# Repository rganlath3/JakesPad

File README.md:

# JakesPad
A custom built fighting gamepad controller for arcade style games. This controller is custom sized for "Jake". It uses a raspberry pi 2040 chipset along with Kailh keyswitches with a custom 3D printed enclosure and PCB.
This is based on jfedor2's flatbox rev5 design. I reverse engineered the PCB from his design here: https://github.com/jfedor2/flatbox.git

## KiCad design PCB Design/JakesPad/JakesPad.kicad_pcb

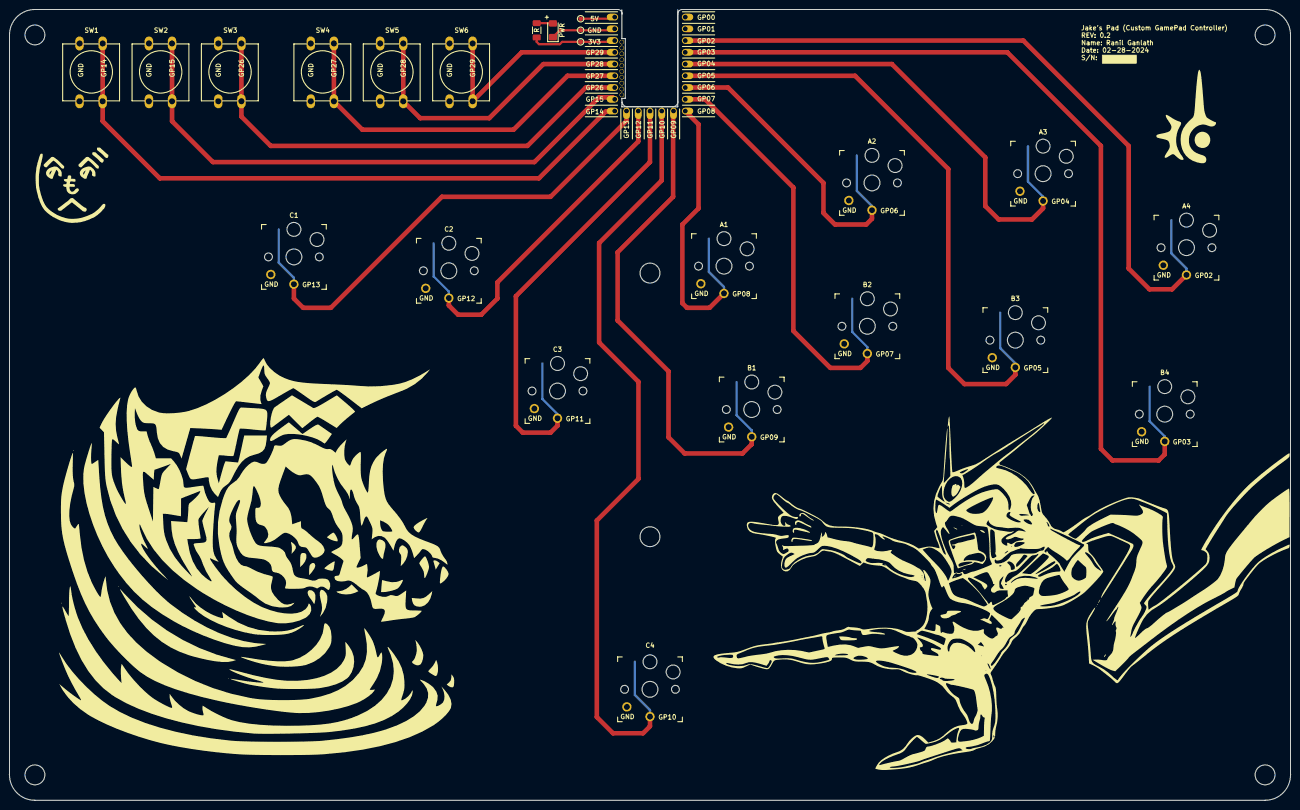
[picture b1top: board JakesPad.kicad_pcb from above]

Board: 2 copper layers, 277.0 x 171.0 mm, 30 parts (0 on the bottom side), 22 nets.

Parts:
3V3, 5V: TestPoint; TestPoint_Pad_D1.0mm
A1, A2, A3, A4: SW_DIP_x01; Kailh_socket_PG1350_optional
B1, B2, B3, B4: SW_DIP_x01; Kailh_socket_PG1350_optional
C1, C2, C3, C4: SW_DIP_x01; Kailh_socket_PG1350_optional
GND: TestPoint; TestPoint_Pad_D1.0mm
H1, H2, H3, H4, H5, H6: MountingHole; MountingHole_4.3mm_M4
PWR: 5V LED; LED_1206_3216Metric_Pad1.42x1.75mm_HandSolder
R: 200ohm; R_1206_3216Metric_Pad1.30x1.75mm_HandSolder
SW1, SW2, SW3, SW4, SW5, SW6: SW_Push; SW_PUSH-12mmWithCAD
U2: rp2040-zero; rp2040-zero-tht-pads-cutout

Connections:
+3.3V: 3V3.1, R.1, U2.21 (3V3)
+5V: 5V.1, U2.23 (5V)
GND: A1.2, A2.2, A3.2, A4.2, B1.2, B2.2, B3.2, B4.2, C1.2, C2.2, C3.2, C4.2, GND.1, PWR.1 (K), SW1.1, SW2.1, SW3.1, SW4.1, SW5.1, SW6.1, U2.22 (GND)
unnamed: PWR.2 (A), R.2
unnamed: A4.1, U2.3 (2)
unnamed: B4.1, U2.4 (3)
unnamed: A3.1, U2.5 (4)
unnamed: B3.1, U2.6 (5)
unnamed: A2.1, U2.7 (6)
unnamed: B2.1, U2.8 (7)
unnamed: A1.1, U2.9 (8)
unnamed: B1.1, U2.10 (9)
unnamed: C4.1, U2.11 (10)
unnamed: C3.1, U2.12 (11)
unnamed: C2.1, U2.13 (12)
unnamed: C1.1, U2.14 (13)
unnamed: SW1.2, U2.15 (14)
unnamed: SW2.2, U2.16 (15)
unnamed: SW3.2, U2.17 (26)
unnamed: SW4.2, U2.18 (27)
unnamed: SW5.2, U2.19 (28)
unnamed: SW6.2, U2.20 (29)

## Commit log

2024-02-23 Initial Commit
    No desc hahahaha.
2024-03-10 Big Update
2024-05-17 PCB Design Updates for New Finger Positions
2024-05-22 Project Cleanup
2024-06-15 Need to update component placement and add RGB.
